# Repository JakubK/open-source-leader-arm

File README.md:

# Changes made in this fork, original readme below

## PCB 

Added custom PCB which applies [JLCPCB design rules](https://github.com/labtroll/KiCad-DesignRules). It allows to mount either esp32 or raspberry pi pico after flashing custom firmware.

Each encoder DIR port was split into DIR+ and DIR-. DIR- resembles DIR from original project and is tied to GND, while conversely DIR+ is tied to the 3V3 from the Board, allowing to switch encoder direction in case the magnet polarity is wrong, which can be noticed in the simulation.

It can be mounted on the original arm base in the place of solderboard, using 4 M2 bolts of 4mm length and heat inserts for them.

# Open-source Leader Arm

Open-source, low-cost, 3D-printed leader arm for teleoperating an SO-ARM 

https://github.com/user-attachments/assets/977a0b56-c7d2-4a90-b86a-445dd3963871

A leader arm is moved by an operator to teleoperate a follower robot arm. A leader arm's joints are never driven, they simply report their joint angles, which the follower mirrors. So instead of using expensive servos, a cheap magnetic encoder like the AS5600 can be used. It results in an arm which is lighter to move by hand and is much cheaper than the one built with servos. 

Currently, the leader arm is tested against a simulated SO-ARM in MuJoCo with live physics, so you can pick up and move objects in the scene without a physical follower arm. It also plugs into LeRobot as a teleoperator, so you can record training datasets entirely in simulation.

## Featured Build

Oliver Choy independently built the Leader Arm and documented the process, including the ROS 2 implementation. He'll also be showcasing it at ROSCon 2026. [Read about his build →](https://www.linkedin.com/pulse/building-sub-50-3d-printed-robotic-arm-ros-2-little-oliver-choy-22amc/)

## Bill of materials

|Component| Quantity | Price|
|-|-|-|
|AS5600 encoder + Diametric magnet (5mm dia,2mm thick) | 6 | 6 x 186 INR = 1,116 INR (~11.7 USD)|
|608 Bearing (8x22x7mm) | 6 | 6 x 30 INR = 180 INR (~1.9 USD)|
| CJMCU TCA9548A I2C 8 Channel Multiplexer| 1 | 59 INR (~0.6 USD)|
|ESP32 | 1 | 550 INR (~5.8 USD)|
|28 AWG Silicon Wires | ~5m per color (4 colors) | 477 INR (~ 5 USD)|
|M3x10mm screws | 60 | 195 INR (~2 USD)|
|7x9cm Perfboard | 1 | 42 INR (~0.45 USD)|
| Rubber band | 1 | Negligible|
| |Total | 2,619 INR (~27.45 USD)|

Excluding the price of the 3D printed parts.

For context: the STS3215 servo used in the standard LeRobot leader arm costs around 24 USD each, and the leader arm needs six, roughly 144 USD in servos alone. Our entire component list comes in under 28 USD.

Note: The encoder and diametric magnet almost always come as a combo. Try to buy them together, the diametric magnet on its own can be difficult to source. 

## How it works?

**Why a mux?** - The AS5600 encoder has a fixed I2C address (0x36) and can't be changed. So we can't put more than one on a bus as they will all share the same address. The TCA9548A mux gives each encoder its own separate channel and connects one channel to the ESP32 at a time, so all six encoders can be read without any collision. 

## Wiring

| TCA9548A | ESP32 | 
| ------ | ------ |
| VIN | 3V3 |
| GND | GND |
| SDA | D18 |
| SCL | D19 |
| RST | 3V3 |
| A0, A1, A2 | GND |

| AS5600 | ESP32 |
| ------ | ------ |
| VCC | 3V3 |
| GND, DIR | GND |

| AS5600 | TCA9548A |
|--------|----------|
| SDA | SDn |
| SCL | SCn |

n = the channel for that joint \
joint 0 → SD0/SC0, ... joint 5 → SD5/SC5

## Print Settings

Printed in PLA, 0.2mm layer height and 15% infill.

There are 19 unique parts and a total of 49 parts. All the parts are designed to not need support while printing. All the parts are already oriented for printing; if any part loads at an odd angle, lay its flat face on the bed. 

The part 'bearing_housing' needs a bearing inserted mid-print. Add a pause at 10mm height (layer 50 at 0.2mm layer height setting). In Bambu studio, right-click the corresponding layer on the vertical slider and choose "Add Pause". When the printer pauses, insert the 608 bearing into the pocket, make sure it is seated flat, and then resume.

### Parts list and count

```
1 x base
1 x base_connector
6 x bearing_housing
6 x encoder_housing
5 x encoder_housing_cap
6 x rotor 
3 x link_perpendicular_base
3 x link_perpendicular_body
1 x link_shoulder_to_elbow
1 x link_elbow_to_wrist
1 x link_tooltip 
3 x washer_perpendicular_link 
3 x washer_round
1 x handle_base
1 x handle_body
1 x rest_pose_holder_base
1 x rest_pose_holder_body
3 x wire_holder
2 x rubberband_housing
```

## Firmware

Flash firmware.ino to the ESP32 using the Arduino IDE: 

1. Install the ESP32 board support (Tools → Board → Boards Manager → search "esp32")
2. Open 'firmware/firmware.ino' and select your ESP32 board and port, and upload.
3. After uploading, open the serial monitor at **115200 baud rate** to check the output.

The firmware uses only the built-in 'Wire' library, so there's nothing else to install.

On boot it prints a channel scan, one line per channel, naming whatever is wrong: "no device at 0x36" for a wiring or power fault, or "magnet too weak / too far", "too strong / too close" or "not detected" for a magnet fault.

If everything works then it prints "magnet ok"

Example : # ch0: AS5600 found, magnet ok, raw 1234

After the scan, it streams the six encoder readings as a comma-separated line, at 100 Hz. A channel that cannot be read sends "-1" in place of its angle.

## Running the software

Two ways to drive the follower arm: using LeRobot plugins (recommended), which work with a physical or a simulated follower, or the standalone scripts, which drive the simulated follower only. The follower arm in both methods starts in the SO-ARM rest pose, so hold the leader in its reference pose and press ENTER when prompted. That aligns both arms.

### Simulator setup

Skip this if you are using a physical follower. The simulator needs the SO-ARM model from MuJoCo Menagerie; the full repo is 2.35 GB, so pull only the SO-ARM100 folder (6.5 MB).
From the repo root:
```bash
git clone --depth 1 --filter=blob:none --sparse https://github.com/google-deepmind/mujoco_menagerie.git
cd mujoco_menagerie
git sparse-checkout set trs_so_arm100
cd ..
```
### Method 1 - using LeRobot plugins

Two plugins in this repo make the arm work inside [LeRobot](https://github.com/huggingface/lerobot):

- `lerobot_teleoperator_encoder_leader` - registers this leader arm as a LeRobot `Teleoperator`, so it replaces the servo leader in LeRobot's standard commands.
- `lerobot_robot_mujoco_so_arm` - registers a MuJoCo-simulated SO-ARM100 as a LeRobot `Robot`, so you can run the whole pipeline without a physical follower.

From the repo root (Python 3.10 or newer):
```bash
pip install lerobot
pip install -e lerobot_teleoperator_encoder_leader
pip install -e lerobot_robot_mujoco_so_arm
```

#### Teleoperate the arm

```bash
lerobot-teleoperate `
  --robot.type=so101_follower --robot.port=COM6 --robot.id=my_follower `
  --teleop.type=encoder_leader --teleop.port=COM3 --teleop.id=my_leader
```

Replace `COM3` with your ESP32's port. It's the same one the Arduino IDE showed when you flashed the firmware; on Linux and macOS it looks like `/dev/ttyUSB0`. Replace `COM6` with your follower's port.

When prompted, make sure the follower is in its rest pose, then hold the leader in its reference pose and press ENTER. That zeroes the encoders against the follower's rest pose.

Swap `--robot.type=mujoco_so_arm --robot.id=sim --robot.scene=mujoco_menagerie/trs_so_arm100/scene.xml` and drop `--robot.port` to drive the follower in simulation.

#### Record a dataset with a physical follower

```bash
lerobot-record `
  --robot.type=so101_follower --robot.port=COM6 --robot.id=my_follower `
  --robot.cameras="{top: {type: opencv, index_or_path: 0, width: 640, height: 480, fps: 30}, wrist: {type: opencv, index_or_path: 1, width: 640, height: 480, fps: 30}}" `
  --teleop.type=encoder_leader --teleop.port=COM3 --teleop.id=my_leader `
  --dataset.repo_id=<hf_user>/so_arm_sort --dataset.num_episodes=50 `
  --dataset.single_task="Put the red block in the left bin"
```
Replace `<hf_user>` with your huggingface username.
For more, see [Record a dataset](https://huggingface.co/docs/lerobot/main/en/lerobot-dataset-v3#record-a-dataset) in the LeRobot docs.

#### Record a dataset in simulation

```bash
lerobot-record `
  --robot.type=mujoco_so_arm --robot.id=sim `
  --robot.scene=mujoco_menagerie/trs_so_arm100/scene.xml --robot.viewer=true `
  --teleop.type=encoder_leader --teleop.port=COM3 --teleop.id=my_leader `
  --dataset.repo_id=<hf_user>/so_arm_sort --dataset.num_episodes=50 `
  --dataset.single_task="Put the red block in the left bin"
```
Replace `<hf_user>` with your huggingface username.
The scene comes with a block-sorting task: three coloured blocks and three matching bins.

Between episodes the blocks get rearranged into new positions. The plugin watches the same keys `lerobot-record` already uses (Right/Left, or `n`/`r`), so there is nothing extra to press and nothing to do during the reset window.

If you end episodes by timeout rather than by keypress, match both of `lerobot-record`'s timers or the episode tracking drifts:

```bash
  --dataset.episode_time_s=30 --robot.episode_time_s=30 `
  --dataset.reset_time_s=10  --robot.reset_time_s=10
```

Set the recording rate with `--dataset.fps` (default is 30). On integrated graphics 30 is about the limit; drop to 25 if the loop lags behind it.

Shadows and reflections are left out of the recorded images to keep the render cheap.

### Method 2 - using standalone scripts

No LeRobot needed; the encoder stream drives MuJoCo directly.

```bash
pip install "mujoco>=3.2" pyserial
```
Run either one.
```bash
python teleop.py --port COM3              # plain teleop, empty scene
python teleop_sort_task.py --port COM3    # teleop + block sorting
```

On Linux, the port looks like `/dev/ttyUSB0`.

In `teleop_sort_task.py`, press `R` in the viewer to reset the blocks.

## Assembly guide

This leader arm has six joints, `joint_0` to `joint_5`.
### Before you start : 
- See the print settings section for the full parts list and count
- Use the images in the guide for parts orientation and alignment. The assembly files under cad_files are also helpful for this.
- Notation : A + B means "attach part B to part A or assembly A". assembly_step_N refers to the result of step N. 
- Only joint_0 and joint_5 get their encoder attached immediately. The remaining four joints get their encoders at the very end, so that there is less wire clutter during the assembly.
 
### Steps : 
1. Start by wiring all the six encoders as shown in `wiring.png`.
2. insert the diametric magnet into the circular pocket provided in the `rotor` (for all 6 rotors)
3. `rotor + bearing_housing + link_perpendicular_base + link_perpendicular_body + washer_perpendicular_link` (`joint_0`)
4. `assembly_step_3 + base_connector` 
5. `assembly_step_4 + encoder_housing + AS5600_encoder` 
6. Tie a knot in the wire, then attach the `encoder_housing_cap`, so that a wire pull doesn't act on the encoder. 
7. `assembly_step_6 + base` 
8. `assembly_step_7 + rest_pose_holder_base + rest_pose_holder_body` 
9. `assembly_step_8 + bearing_housing` 
10. `assembly_step_9 + rotor + link_shoulder_to_elbow + washer_round` (`joint_1`) 
11. `link_shoulder_to_elbow + bearing_housing` (similar to step 9)
12. `assembly_step_11 + rotor + link_elbow_to_wrist + washer_round` (similar to step 10) (`joint_2`)
13. `link_elbow_to_wrist + bearing_housing` (similar to step 11)
14. `assembly_step_13 + rotor + link_perpendicular_base + link_perpendicular_body + washer_perpendicular_link` (similar to step 3) (`joint_3`)
15. `assembly_step_14 + bearing_housing` (similar to step 9)
16. `assembly_step_15 + rotor + link_perpendicular_base + link_perpendicular_body + washer_perpendicular_link` (similar to step 14) (`joint_4`)
17. `assembly_step_16 + bearing_housing` (similar to steps 9 and 15)
18. `assembly_step_17 + rotor + link_tooltip + washer_round` (`joint_5`)
19. `assembly_step_18 + encoder_housing + AS5600_encoder`
20. Tie a knot in the wire as in step 6
21. `assembly_step_20 + handle_base` (the `handle_base` also acts here as the `encoder_housing_cap`) 
22. `assembly_step_21 + handle_body` 
23. attach the three `wire_holder`s on `link_shoulder_to_elbow` and `link_elbow_to_wrist`. 
24. Route a single rubberband through both `rubberband_housings`, then fix one housing to `link_shoulder_to_elbow` and one to `link_elbow_to_wrist`. 
25. attach the `encoder_housing + AS5600_encoder`, tie a knot, and attach the `encoder_housing_cap` for the four remaining joints, in the same way as step 5 or step 19. 

## Acknowledgements

This project builds on the work of several open-source projects:

- [SO-ARM100](https://github.com/TheRobotStudio/SO-ARM100) - the follower arm design this leader is built to teleoperate.
- [LeRobot](https://github.com/huggingface/lerobot) - the leader/follower teleoperation approach this project is based on.
- [MuJoCo Menagerie](https://github.com/google-deepmind/mujoco_menagerie) - the SO-ARM model used by the simulated follower.

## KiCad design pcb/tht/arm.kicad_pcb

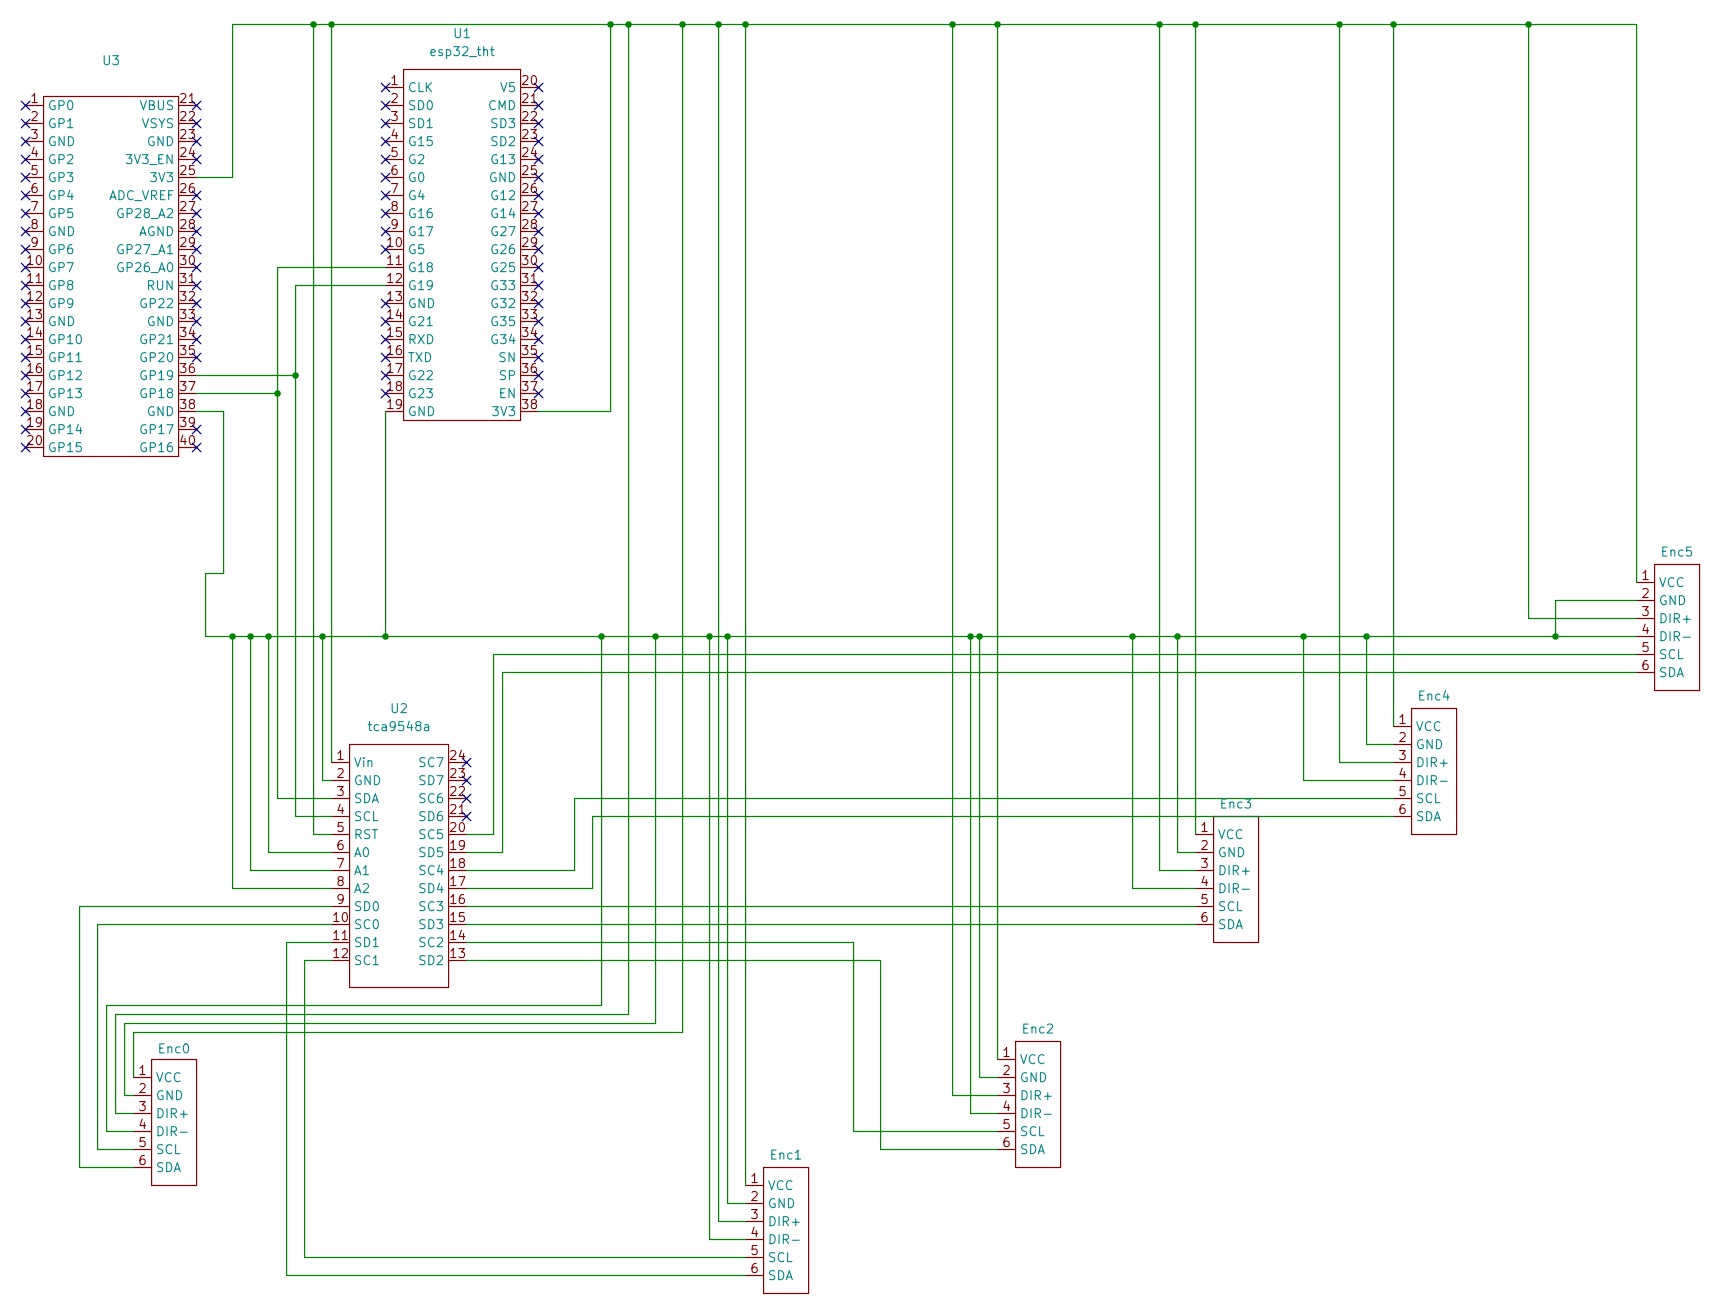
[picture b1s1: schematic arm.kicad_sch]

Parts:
Enc0, Enc1, Enc2, Enc3, Enc4, Enc5: AS5600_THT
U1: esp32_tht
U2: tca9548a; TCA9548A_THT
U3: pico_tht

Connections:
unnamed: Enc0.1 (VCC), Enc0.3 (DIR+), Enc1.1 (VCC), Enc1.3 (DIR+), Enc2.1 (VCC), Enc2.3 (DIR+), Enc3.1 (VCC), Enc3.3 (DIR+), Enc4.1 (VCC), Enc4.3 (DIR+), Enc5.1 (VCC), Enc5.3 (DIR+), U1.38 (3V3), U2.1 (Vin), U2.5 (RST), U3.25 (3V3)
unnamed: Enc0.2 (GND), Enc0.4 (DIR-), Enc1.2 (GND), Enc1.4 (DIR-), Enc2.2 (GND), Enc2.4 (DIR-), Enc3.2 (GND), Enc3.4 (DIR-), Enc4.2 (GND), Enc4.4 (DIR-), Enc5.2 (GND), Enc5.4 (DIR-), U1.19 (GND), U2.2 (GND), U2.6 (A0), U2.7 (A1), U2.8 (A2), U3.38 (GND)
unnamed: Enc0.5 (SCL), U2.10 (SC0)
unnamed: Enc0.6 (SDA), U2.9 (SD0)
unnamed: Enc1.5 (SCL), U2.12 (SC1)
unnamed: Enc1.6 (SDA), U2.11 (SD1)
unnamed: Enc2.5 (SCL), U2.14 (SC2)
unnamed: Enc2.6 (SDA), U2.13 (SD2)
unnamed: Enc3.5 (SCL), U2.16 (SC3)
unnamed: Enc3.6 (SDA), U2.15 (SD3)
unnamed: Enc4.5 (SCL), U2.18 (SC4)
unnamed: Enc4.6 (SDA), U2.17 (SD4)
unnamed: Enc5.5 (SCL), U2.20 (SC5)
unnamed: Enc5.6 (SDA), U2.19 (SD5)
unnamed: U1.11 (G18), U2.3 (SDA), U3.37 (GP18)
unnamed: U1.12 (G19), U2.4 (SCL), U3.36 (GP19)

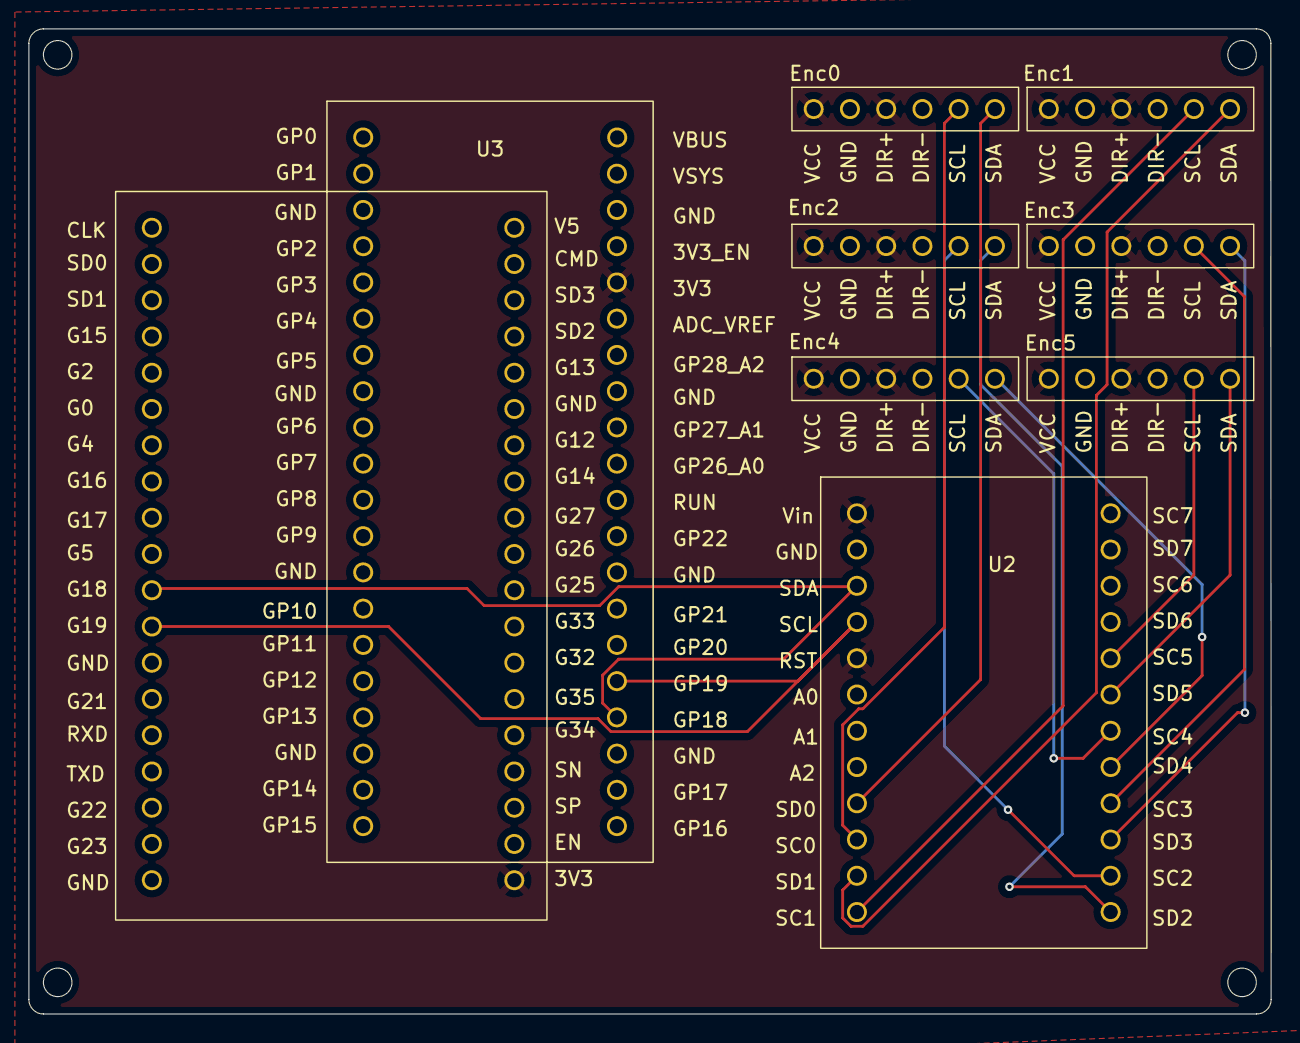
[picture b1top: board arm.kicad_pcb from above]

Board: 2 copper layers, 87.1 x 69.0 mm, 9 parts (0 on the bottom side), 16 nets.
